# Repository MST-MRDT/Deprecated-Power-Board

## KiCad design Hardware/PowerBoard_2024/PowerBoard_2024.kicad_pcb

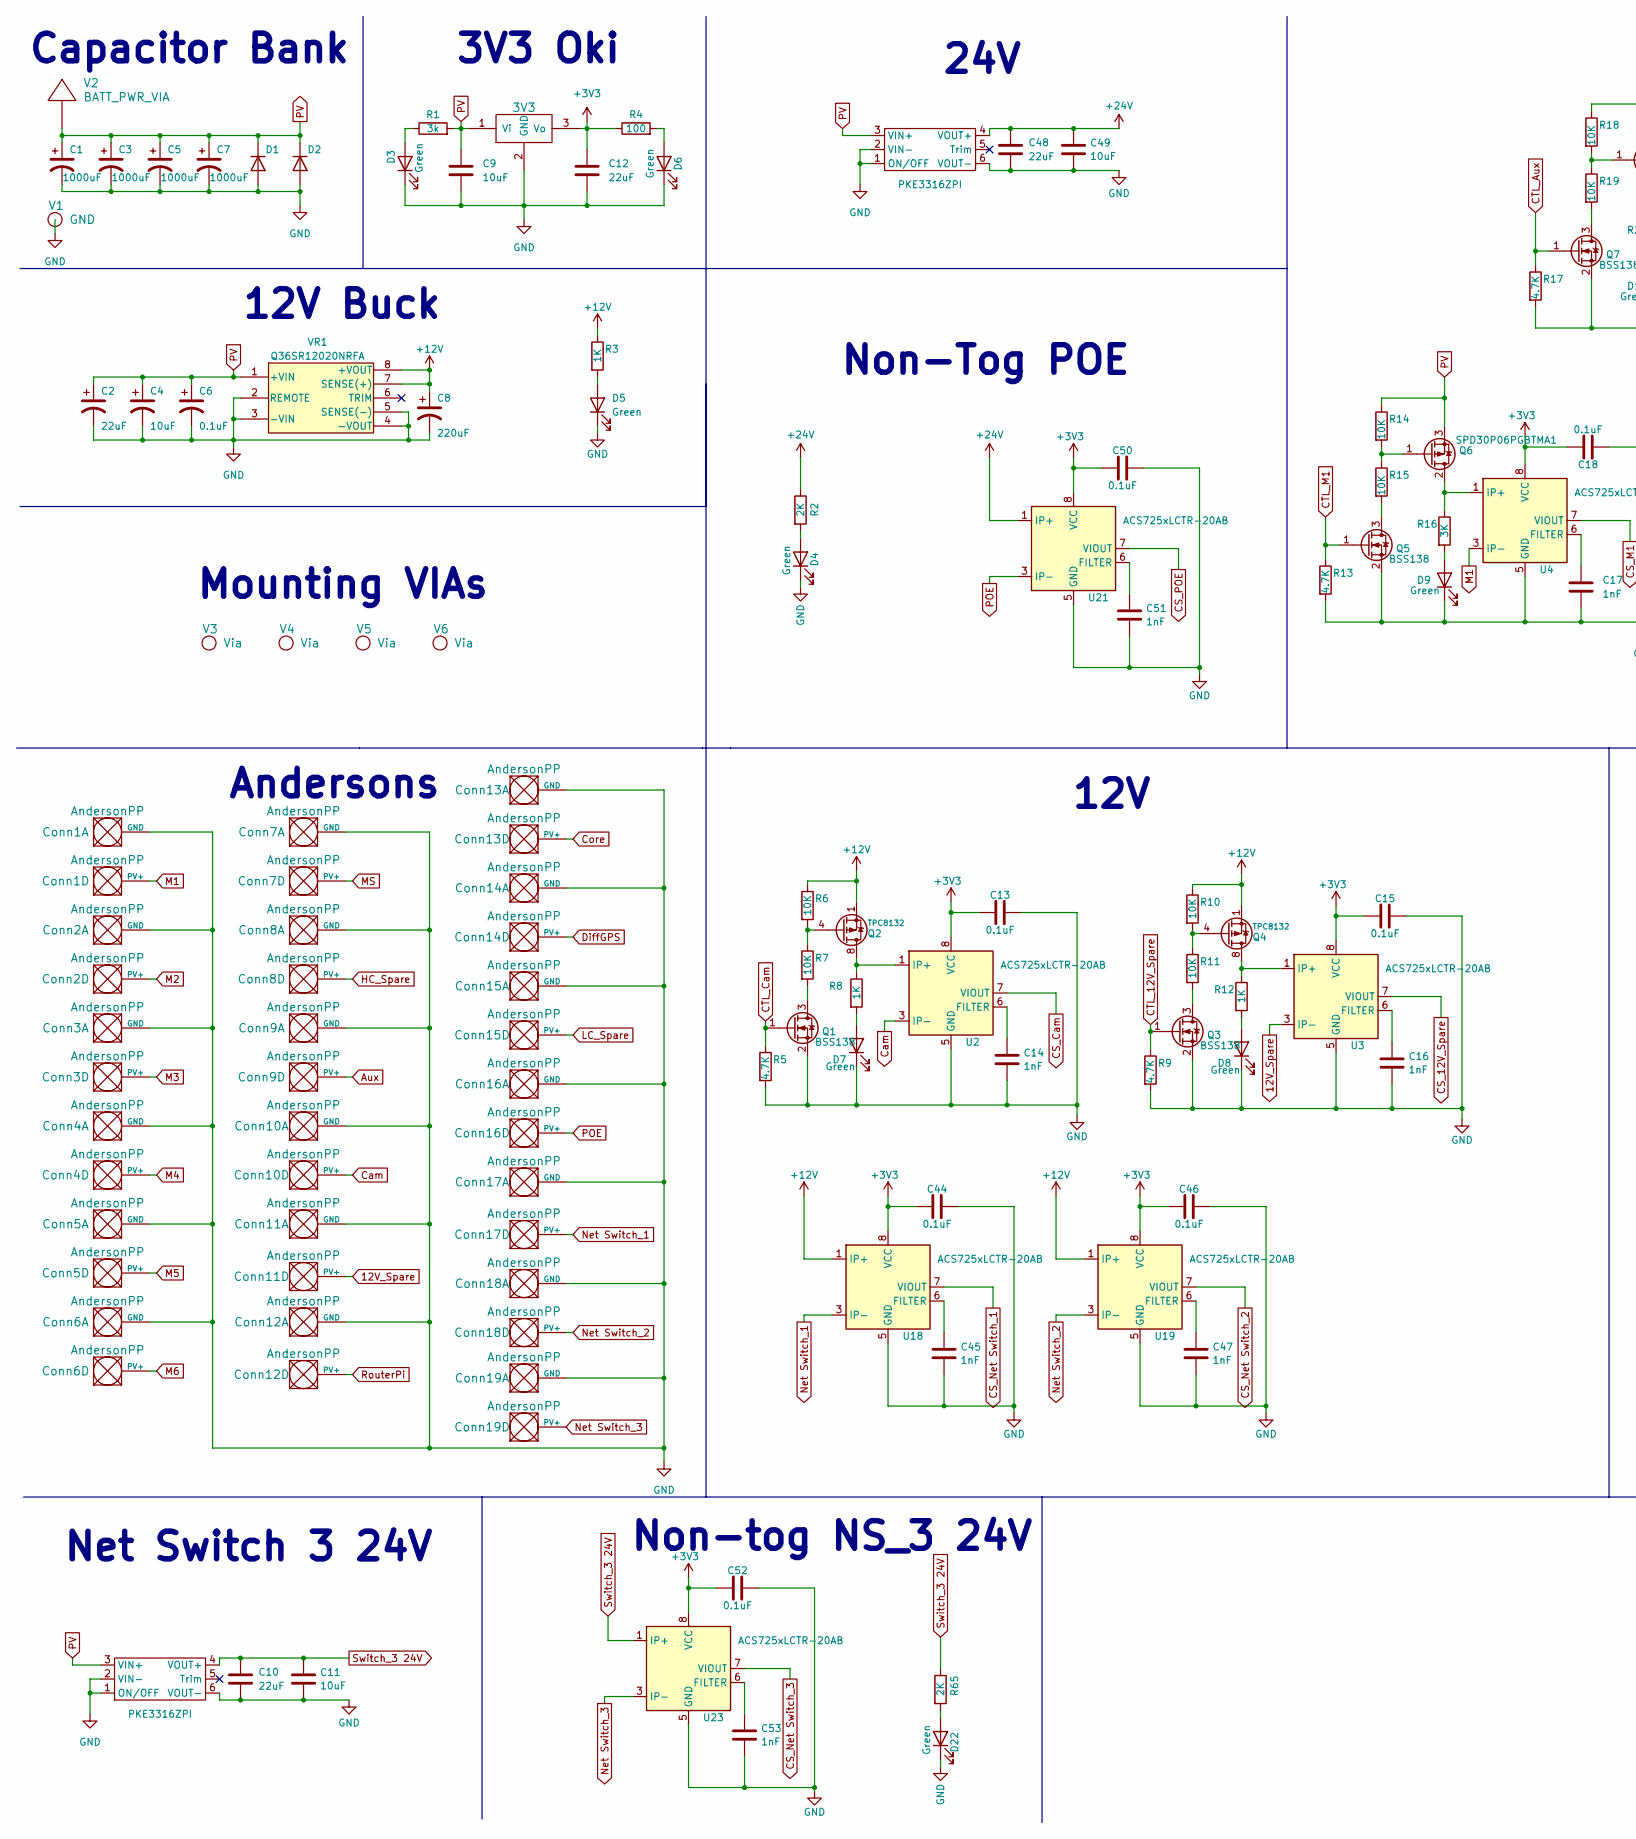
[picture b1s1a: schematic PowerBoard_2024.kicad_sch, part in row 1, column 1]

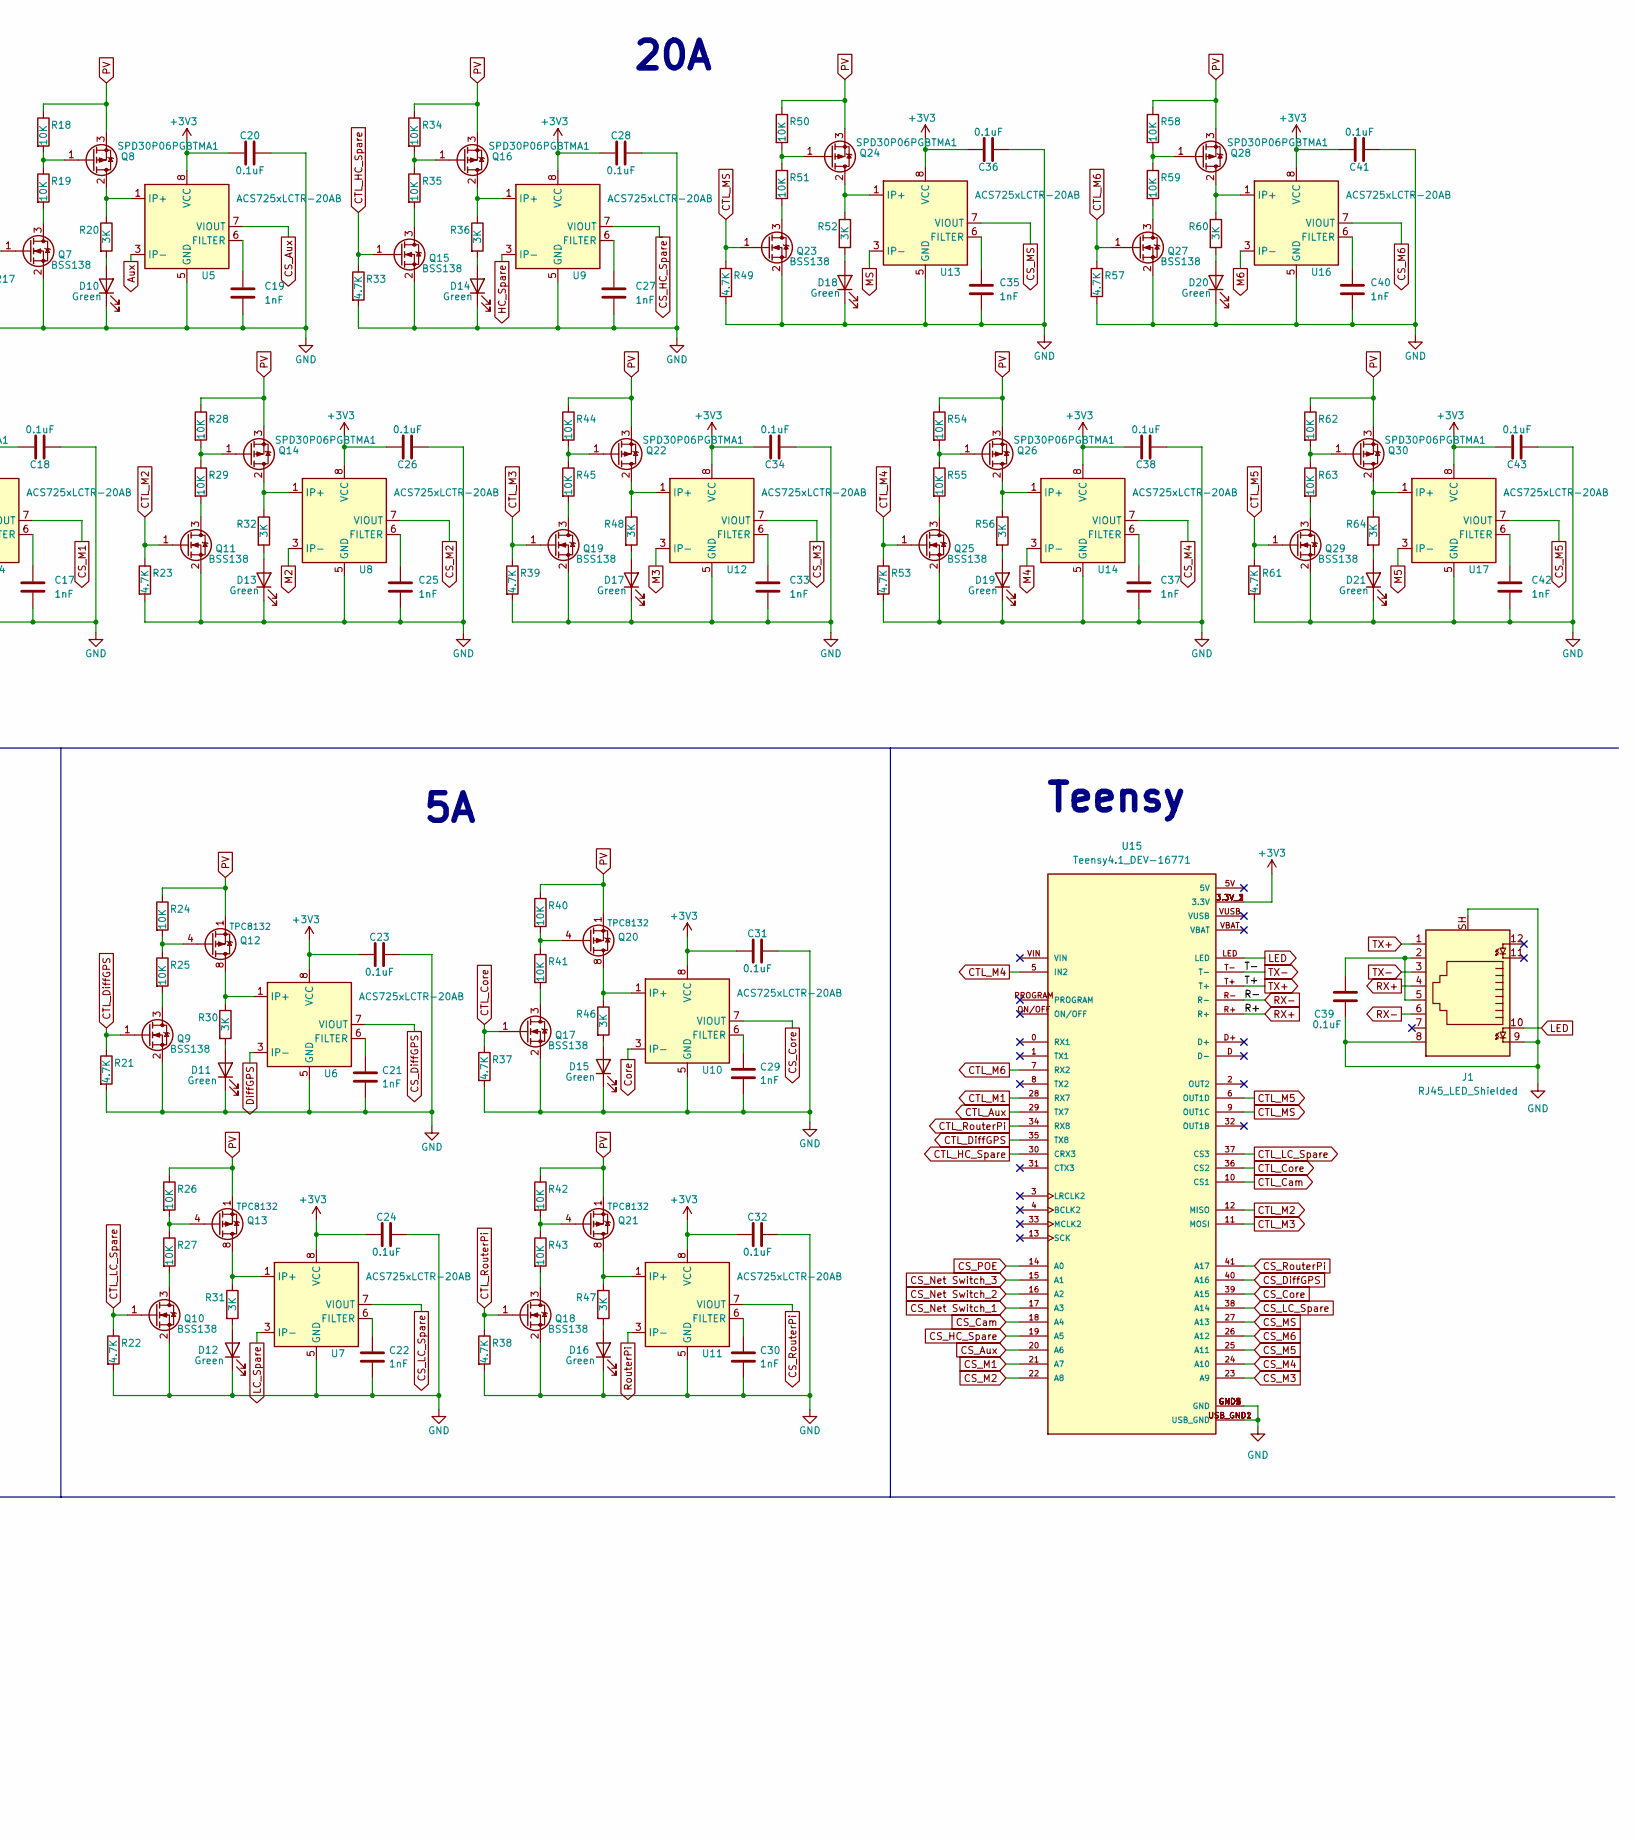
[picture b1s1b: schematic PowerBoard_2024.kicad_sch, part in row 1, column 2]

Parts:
C1, C3, C5, C7: 1000uF; CP_Radial_D16.0mm_P7.50mm
C2, C10, C48: 22uF; CP_Radial_D5.0mm_P2.00mm
C4, C9, C11, C49: 10uF; C_1206_3216Metric_Pad1.33x1.80mm_HandSolder
C6: 0.1uF; C_1206_3216Metric_Pad1.33x1.80mm_HandSolder
C8: 220uF; CP_Radial_D6.3mm_P2.50mm
C12: 22uF; C_0603_1608Metric_Pad1.08x0.95mm_HandSolder
C13, C15, C18, C20, C23, C24, C26, C28, C31, C32, C34, C36, C38, C39, C41, C43, C44, C46, C50, C52: 0.1uF; C_0603_1608Metric_Pad1.08x0.95mm_HandSolder
C14, C16, C17, C19, C21, C22, C25, C27, C29, C30, C33, C35, C37, C40, C42, C45, C47, C51, C53: 1nF; C_0603_1608Metric_Pad1.08x0.95mm_HandSolder
Conn1, Conn2, Conn3, Conn4, Conn5, Conn6, Conn7, Conn8, Conn9, Conn10, Conn11, Conn12, Conn13, Conn14, Conn15, Conn16, Conn17, Conn18, Conn19: AndersonPP; Square_Anderson_2_H_Stacked
D1, D2: 1.5KE36A+; D_DO-201_P5.08mm_Vertical_KathodeUp
D3, D4, D5, D6, D7, D8, D9, D10, D11, D12, D13, D14, D15, D16, D17, D18, D19, D20, D21, D22: Green; LED_0603_1608Metric_Pad1.05x0.95mm_HandSolder
J1: RJ45_LED_Shielded; RJ45_Teensy
Q1, Q3, Q5, Q7, Q9, Q10, Q11, Q15, Q17, Q18, Q19, Q23, Q25, Q27, Q29: BSS138; SOT-23
Q2, Q4, Q12, Q13, Q20, Q21: TPC8132; SOIC-8_3.9x4.9mm_P1.27mm
Q6, Q8, Q14, Q16, Q22, Q24, Q26, Q28, Q30: SPD30P06PGBTMA1; TO-252-2
R1: 3k; R_0603_1608Metric_Pad0.98x0.95mm_HandSolder
R2, R65: 2K; R_0603_1608Metric_Pad0.98x0.95mm_HandSolder
R3, R8, R12: 1K; R_0603_1608Metric_Pad0.98x0.95mm_HandSolder
R4: 100; R_0603_1608Metric_Pad0.98x0.95mm_HandSolder
R5, R9, R13, R17, R21, R22, R23, R33, R37, R38, R39, R49, R53, R57, R61: 4.7K; R_0603_1608Metric_Pad0.98x0.95mm_HandSolder
R6, R7, R10, R11, R14, R15, R18, R19, R24, R25, R26, R27, R28, R29, R34, R35, R40, R41, R42, R43, R44, R45, R50, R51, R54, R55, R58, R59, R62, R63: 10K; R_0603_1608Metric_Pad0.98x0.95mm_HandSolder
R16, R20, R30, R31, R32, R36, R46, R47, R48, R52, R56, R60, R64: 3K; R_0603_1608Metric_Pad0.98x0.95mm_HandSolder
U1: 3V3; OKI_Horizontal
U2, U3, U6, U7, U10, U11, U18, U19: ACS725xLCTR-20AB; SOP-8_3.9x4.9mm_P1.27mm
U4, U5, U8, U9, U12, U13, U14, U16, U17, U21, U23: ACS725xLCTR-20AB; SOIC-8_3.9x4.9mm_P1.27mm
U15: Teensy4.1_DEV-16771; Teensy_4_1_Ethernet; PARTREV 4.1
U20, U22: PKE3316ZPI
V1: GND; BATT_PWR_VIA
V2: BATT_PWR_VIA
V3, V4, V5, V6: Via; 4_40_Hole_Corner
VR1: Q36SR12020NRFA

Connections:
12V_Spare: Conn11.4 (PV+), U3.3 (IP-), U3.4 (IP-)
+3V3: C12.1, C13.1, C15.1, C18.2, C20.1, C23.1, C24.1, C26.2, C28.1, C31.1, C32.1, C34.2, C36.2, C38.2, C41.2, C43.2, C44.1, C46.1, C50.1, C52.1, R4.1, U1.3 (Vo), U2.8 (VCC), U3.8 (VCC), U4.8 (VCC), U5.8 (VCC), U6.8 (VCC), U7.8 (VCC), U8.8 (VCC), U9.8 (VCC), U10.8 (VCC), U11.8 (VCC), U12.8 (VCC), U13.8 (VCC), U14.8 (VCC), U15.3.3V_1 (3.3V), U15.3.3V_2 (3.3V), U15.3.3V_3 (3.3V), U16.8 (VCC), U17.8 (VCC), U18.8 (VCC), U19.8 (VCC), U21.8 (VCC), U23.8 (VCC)
+12V: C8.1, Q2.1 (S), Q2.2 (S), Q2.3 (S), Q4.1 (S), Q4.2 (S), Q4.3 (S), R3.1, R6.1, R10.1, U18.1 (IP+), U18.2 (IP+), U19.1 (IP+), U19.2 (IP+), VR1.7 (SENSE(+)), VR1.8 (+VOUT)
+24V: C48.1, C49.1, R2.1, U20.4 (VOUT+), U21.1 (IP+), U21.2 (IP+)
Aux: Conn9.4 (PV+), U5.3 (IP-), U5.4 (IP-)
CS_12V_Spare: U3.7 (VIOUT)
CS_Aux: U5.7 (VIOUT), U15.20 (A6)
CS_Cam: U2.7 (VIOUT), U15.18 (A4)
CS_Core: U10.7 (VIOUT), U15.39 (A15)
CS_DiffGPS: U6.7 (VIOUT), U15.40 (A16)
CS_HC_Spare: U9.7 (VIOUT), U15.19 (A5)
CS_LC_Spare: U7.7 (VIOUT), U15.38 (A14)
CS_M1: U4.7 (VIOUT), U15.21 (A7)
CS_M2: U8.7 (VIOUT), U15.22 (A8)
CS_M3: U12.7 (VIOUT), U15.23 (A9)
CS_M4: U14.7 (VIOUT), U15.24 (A10)
CS_M5: U15.25 (A11), U17.7 (VIOUT)
CS_M6: U15.26 (A12), U16.7 (VIOUT)
CS_MS: U13.7 (VIOUT), U15.27 (A13)
CS_Net Switch_1: U15.17 (A3), U18.7 (VIOUT)
CS_Net Switch_2: U15.16 (A2), U19.7 (VIOUT)
CS_Net Switch_3: U15.15 (A1), U23.7 (VIOUT)
CS_POE: U15.14 (A0), U21.7 (VIOUT)
CS_RouterPi: U11.7 (VIOUT), U15.41 (A17)
CTL_12V_Spare: Q3.1 (G), R9.1
CTL_Aux: Q7.1 (G), R17.1, U15.29 (TX7)
CTL_Cam: Q1.1 (G), R5.1, U15.10 (CS1)
CTL_Core: Q17.1 (G), R37.1, U15.36 (CS2)
CTL_DiffGPS: Q9.1 (G), R21.1, U15.35 (TX8)
CTL_HC_Spare: Q15.1 (G), R33.1, U15.30 (CRX3)
CTL_LC_Spare: Q10.1 (G), R22.1, U15.37 (CS3)
CTL_M1: Q5.1 (G), R13.1, U15.28 (RX7)
CTL_M2: Q11.1 (G), R23.1, U15.12 (MISO)
CTL_M3: Q19.1 (G), R39.1, U15.11 (MOSI)
CTL_M4: Q25.1 (G), R53.1, U15.5 (IN2)
CTL_M5: Q29.1 (G), R61.1, U15.6 (OUT1D)
CTL_M6: Q27.1 (G), R57.1, U15.7 (RX2)
CTL_MS: Q23.1 (G), R49.1, U15.9 (OUT1C)
CTL_RouterPi: Q18.1 (G), R38.1, U15.34 (RX8)
Cam: Conn10.4 (PV+), U2.3 (IP-), U2.4 (IP-)
Core: Conn13.4 (PV+), U10.3 (IP-), U10.4 (IP-)
DiffGPS: Conn14.4 (PV+), U6.3 (IP-), U6.4 (IP-)
GND: C1.2, C2.2, C3.2, C4.2, C5.2, C6.2, C7.2, C8.2, C9.2, C10.2, C11.2, C12.2, C13.2, C14.1, C15.2, C16.1, C17.2, C18.1, C19.1, C20.2, C21.1, C22.1, C23.2, C24.2, C25.2, C26.1, C27.1, C28.2, C29.1, C30.1, C31.2, C32.2, C33.2, C34.1, C35.2, C36.1, C37.2, C38.1, C39.1, C40.2, C41.1, C42.2, C43.1, C44.2, C45.1, C46.2, C47.1, C48.2, C49.2, C50.2, C51.1, C52.2, C53.1, Conn1.1 (GND), Conn2.1 (GND), Conn3.1 (GND), Conn4.1 (GND), Conn5.1 (GND), Conn6.1 (GND), Conn7.1 (GND), Conn8.1 (GND), Conn9.1 (GND), Conn10.1 (GND), Conn11.1 (GND), Conn12.1 (GND), Conn13.1 (GND), Conn14.1 (GND), Conn15.1 (GND), Conn16.1 (GND), Conn17.1 (GND), Conn18.1 (GND), Conn19.1 (GND), D1.2 (A), D2.2 (A), D3.1 (K), D4.1 (K), D5.1 (K), D6.1 (K), D7.1 (K), D8.1 (K), D9.1 (K), D10.1 (K), D11.1 (K), D12.1 (K), D13.1 (K), D14.1 (K), D15.1 (K), D16.1 (K), D17.1 (K), D18.1 (K), D19.1 (K), D20.1 (K), D21.1 (K), D22.1 (K), J1.8, J1.9, J1.SH, Q1.2 (S), Q3.2 (S), Q5.2 (S), Q7.2 (S), Q9.2 (S), Q10.2 (S), Q11.2 (S), Q15.2 (S), Q17.2 (S), Q18.2 (S), Q19.2 (S), Q23.2 (S), Q25.2 (S), Q27.2 (S), Q29.2 (S), R5.2, R9.2, R13.2, R17.2, R21.2, R22.2, R23.2, R33.2, R37.2, R38.2, R39.2, R49.2, R53.2, R57.2, R61.2, U1.2 (GND), U2.5 (GND), U3.5 (GND), U4.5 (GND), U5.5 (GND), U6.5 (GND), U7.5 (GND), U8.5 (GND), U9.5 (GND), U10.5 (GND), U11.5 (GND), U12.5 (GND), U13.5 (GND), U14.5 (GND), U15.GND1 (GND), U15.GND2 (GND), U15.GND3 (GND), U15.GND4 (GND), U15.GND5 (GND), U15.USB_GND1 (USB_GND), U15.USB_GND2 (USB_GND), U16.5 (GND), U17.5 (GND), U18.5 (GND), U19.5 (GND), U20.1 (ON/OFF), U20.2 (VIN-), U20.6 (VOUT-), U21.5 (GND), U22.1 (ON/OFF), U22.2 (VIN-), U22.6 (VOUT-), U23.5 (GND), V1.1, VR1.2 (REMOTE), VR1.3 (-VIN), VR1.4 (-VOUT), VR1.5 (SENSE(-))
HC_Spare: Conn8.4 (PV+), U9.3 (IP-), U9.4 (IP-)
LC_Spare: Conn15.4 (PV+), U7.3 (IP-), U7.4 (IP-)
LED: J1.10, U15.LED
M1: Conn1.4 (PV+), U4.3 (IP-), U4.4 (IP-)
M2: Conn2.4 (PV+), U8.3 (IP-), U8.4 (IP-)
M3: Conn3.4 (PV+), U12.3 (IP-), U12.4 (IP-)
M4: Conn4.4 (PV+), U14.3 (IP-), U14.4 (IP-)
M5: Conn5.4 (PV+), U17.3 (IP-), U17.4 (IP-)
M6: Conn6.4 (PV+), U16.3 (IP-), U16.4 (IP-)
MS: Conn7.4 (PV+), U13.3 (IP-), U13.4 (IP-)
Net Switch_1: Conn17.4 (PV+), U18.3 (IP-), U18.4 (IP-)
Net Switch_2: Conn18.4 (PV+), U19.3 (IP-), U19.4 (IP-)
Net Switch_3: Conn19.4 (PV+), U23.3 (IP-), U23.4 (IP-)
unnamed: C39.2, J1.2, J1.5
unnamed: D3.2 (A), R1.1
unnamed: D4.2 (A), R2.2
unnamed: D5.2 (A), R3.2
unnamed: D6.2 (A), R4.2
unnamed: D7.2 (A), R8.2
unnamed: D8.2 (A), R12.2
unnamed: D9.2 (A), R16.2
unnamed: D10.2 (A), R20.2
unnamed: D11.2 (A), R30.2
unnamed: D12.2 (A), R31.2
unnamed: D13.2 (A), R32.2
unnamed: D14.2 (A), R36.2
unnamed: D15.2 (A), R46.2
unnamed: D16.2 (A), R47.2
unnamed: D17.2 (A), R48.2
unnamed: D18.2 (A), R52.2
unnamed: D19.2 (A), R56.2
unnamed: D20.2 (A), R60.2
unnamed: D21.2 (A), R64.2
unnamed: D22.2 (A), R65.2
unnamed: Q1.3 (D), R7.2
unnamed: Q2.5 (D), Q2.6 (D), Q2.7 (D), Q2.8 (D), R8.1, U2.1 (IP+), U2.2 (IP+)
unnamed: Q2.4 (G), R6.2, R7.1
unnamed: Q3.3 (D), R11.2
unnamed: Q4.5 (D), Q4.6 (D), Q4.7 (D), Q4.8 (D), R12.1, U3.1 (IP+), U3.2 (IP+)
unnamed: Q4.4 (G), R10.2, R11.1
unnamed: Q5.3 (D), R15.2
unnamed: Q6.2 (D), R16.1, U4.1 (IP+), U4.2 (IP+)
unnamed: Q6.1 (G), R14.2, R15.1
unnamed: Q7.3 (D), R19.2
unnamed: Q8.2 (D), R20.1, U5.1 (IP+), U5.2 (IP+)
unnamed: Q8.1 (G), R18.2, R19.1
unnamed: Q9.3 (D), R25.2
unnamed: Q10.3 (D), R27.2
unnamed: Q11.3 (D), R29.2
unnamed: Q12.5 (D), Q12.6 (D), Q12.7 (D), Q12.8 (D), R30.1, U6.1 (IP+), U6.2 (IP+)
unnamed: Q12.4 (G), R24.2, R25.1
unnamed: Q13.5 (D), Q13.6 (D), Q13.7 (D), Q13.8 (D), R31.1, U7.1 (IP+), U7.2 (IP+)
unnamed: Q13.4 (G), R26.2, R27.1
unnamed: Q14.2 (D), R32.1, U8.1 (IP+), U8.2 (IP+)
unnamed: Q14.1 (G), R28.2, R29.1
unnamed: Q15.3 (D), R35.2
unnamed: Q16.2 (D), R36.1, U9.1 (IP+), U9.2 (IP+)
unnamed: Q16.1 (G), R34.2, R35.1
unnamed: Q17.3 (D), R41.2
unnamed: Q18.3 (D), R43.2
unnamed: Q19.3 (D), R45.2
unnamed: Q20.5 (D), Q20.6 (D), Q20.7 (D), Q20.8 (D), R46.1, U10.1 (IP+), U10.2 (IP+)
unnamed: Q20.4 (G), R40.2, R41.1
unnamed: Q21.5 (D), Q21.6 (D), Q21.7 (D), Q21.8 (D), R47.1, U11.1 (IP+), U11.2 (IP+)
unnamed: Q21.4 (G), R42.2, R43.1
unnamed: Q22.2 (D), R48.1, U12.1 (IP+), U12.2 (IP+)
unnamed: Q22.1 (G), R44.2, R45.1
unnamed: Q23.3 (D), R51.2
unnamed: Q24.2 (D), R52.1, U13.1 (IP+), U13.2 (IP+)
unnamed: Q24.1 (G), R50.2, R51.1
unnamed: Q25.3 (D), R55.2
unnamed: Q26.2 (D), R56.1, U14.1 (IP+), U14.2 (IP+)
unnamed: Q26.1 (G), R54.2, R55.1
unnamed: Q27.3 (D), R59.2
unnamed: Q28.2 (D), R60.1, U16.1 (IP+), U16.2 (IP+)
unnamed: Q28.1 (G), R58.2, R59.1
unnamed: Q29.3 (D), R63.2
unnamed: Q30.2 (D), R64.1, U17.1 (IP+), U17.2 (IP+)
unnamed: Q30.1 (G), R62.2, R63.1
unnamed: C14.2, U2.6 (FILTER)
unnamed: C16.2, U3.6 (FILTER)
unnamed: C17.1, U4.6 (FILTER)
unnamed: C19.2, U5.6 (FILTER)
unnamed: C21.2, U6.6 (FILTER)
unnamed: C22.2, U7.6 (FILTER)
unnamed: C25.1, U8.6 (FILTER)
unnamed: C27.2, U9.6 (FILTER)
unnamed: C29.2, U10.6 (FILTER)
unnamed: C30.2, U11.6 (FILTER)
unnamed: C33.1, U12.6 (FILTER)
unnamed: C35.1, U13.6 (FILTER)
unnamed: C37.1, U14.6 (FILTER)
unnamed: C40.1, U16.6 (FILTER)
unnamed: C42.1, U17.6 (FILTER)
unnamed: C45.2, U18.6 (FILTER)
unnamed: C47.2, U19.6 (FILTER)
unnamed: C51.2, U21.6 (FILTER)
unnamed: C53.2, U23.6 (FILTER)
POE: Conn16.4 (PV+), U21.3 (IP-), U21.4 (IP-)
PV: C1.1, C2.1, C3.1, C4.1, C5.1, C6.1, C7.1, C9.1, D1.1 (K), D2.1 (K), Q6.3 (S), Q8.3 (S), Q12.1 (S), Q12.2 (S), Q12.3 (S), Q13.1 (S), Q13.2 (S), Q13.3 (S), Q14.3 (S), Q16.3 (S), Q20.1 (S), Q20.2 (S), Q20.3 (S), Q21.1 (S), Q21.2 (S), Q21.3 (S), Q22.3 (S), Q24.3 (S), Q26.3 (S), Q28.3 (S), Q30.3 (S), R1.2, R14.1, R18.1, R24.1, R26.1, R28.1, R34.1, R40.1, R42.1, R44.1, R50.1, R54.1, R58.1, R62.1, U1.1 (Vi), U20.3 (VIN+), U22.3 (VIN+), V2.1, VR1.1 (+VIN)
RX+: J1.4, U15.R+
RX-: J1.6, U15.R-
RouterPi: Conn12.4 (PV+), U11.3 (IP-), U11.4 (IP-)
Switch_3 24V: C10.1, C11.1, R65.1, U22.4 (VOUT+), U23.1 (IP+), U23.2 (IP+)
TX+: J1.1, U15.T+
TX-: J1.3, U15.T-

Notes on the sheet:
24V
Teensy
12V Buck
Andersons
20A
Capacitor Bank
12V
Non-tog NS_3 24V
Mounting VIAs
Net Switch 3 24V
3V3 Oki
Non-Tog POE

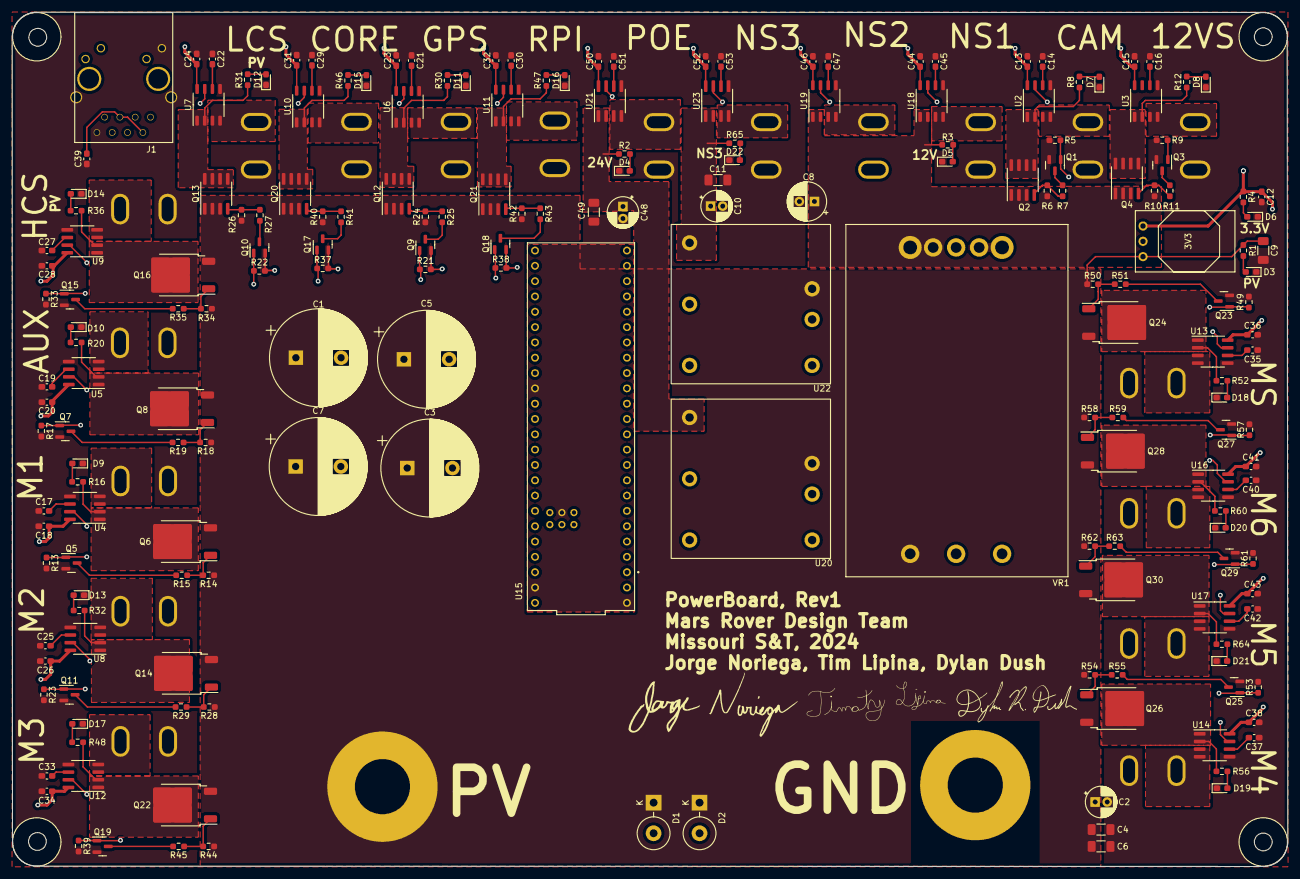
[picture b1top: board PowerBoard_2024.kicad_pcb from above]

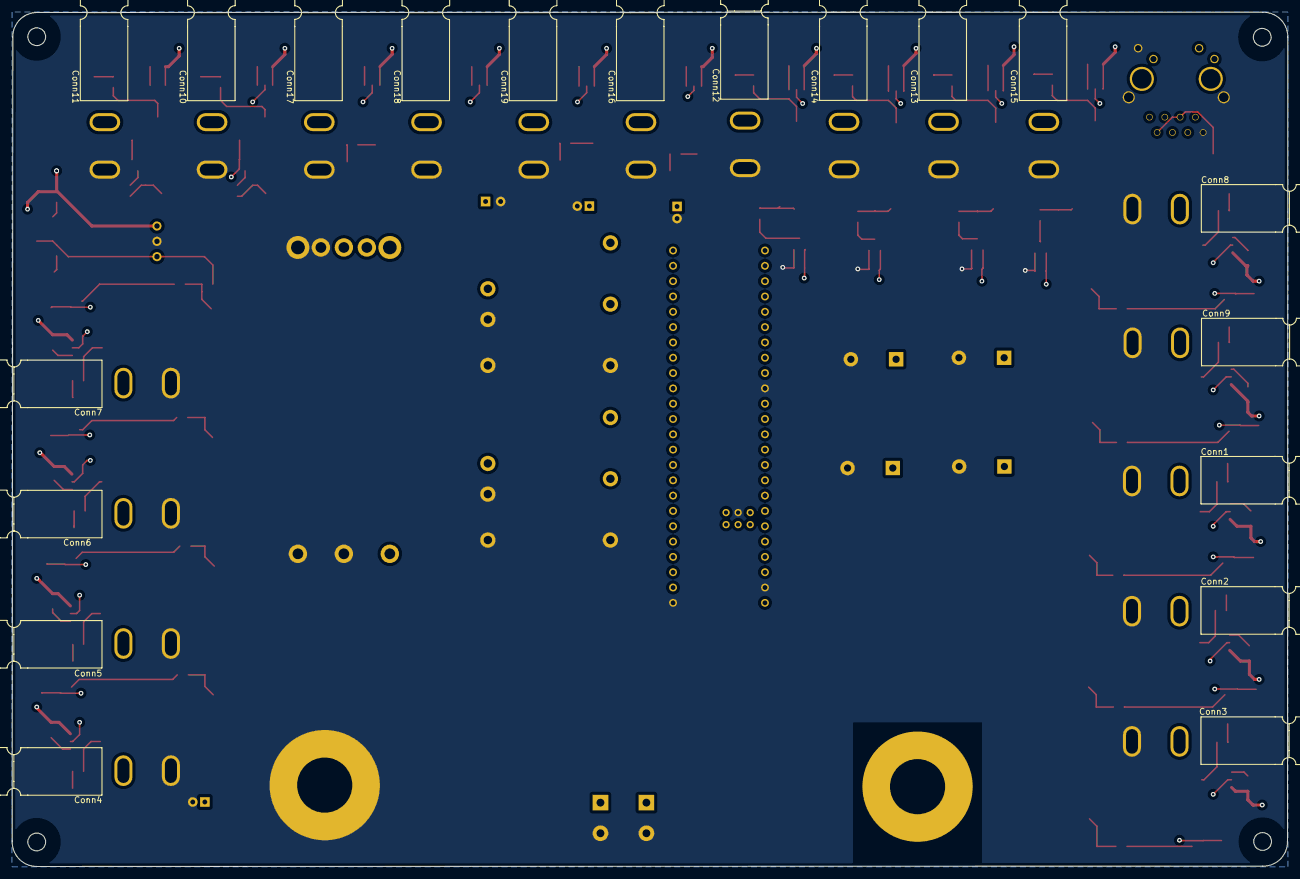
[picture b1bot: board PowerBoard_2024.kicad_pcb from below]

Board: 4 copper layers, 211.5 x 141.6 mm, 220 parts (19 on the bottom side), 148 nets.

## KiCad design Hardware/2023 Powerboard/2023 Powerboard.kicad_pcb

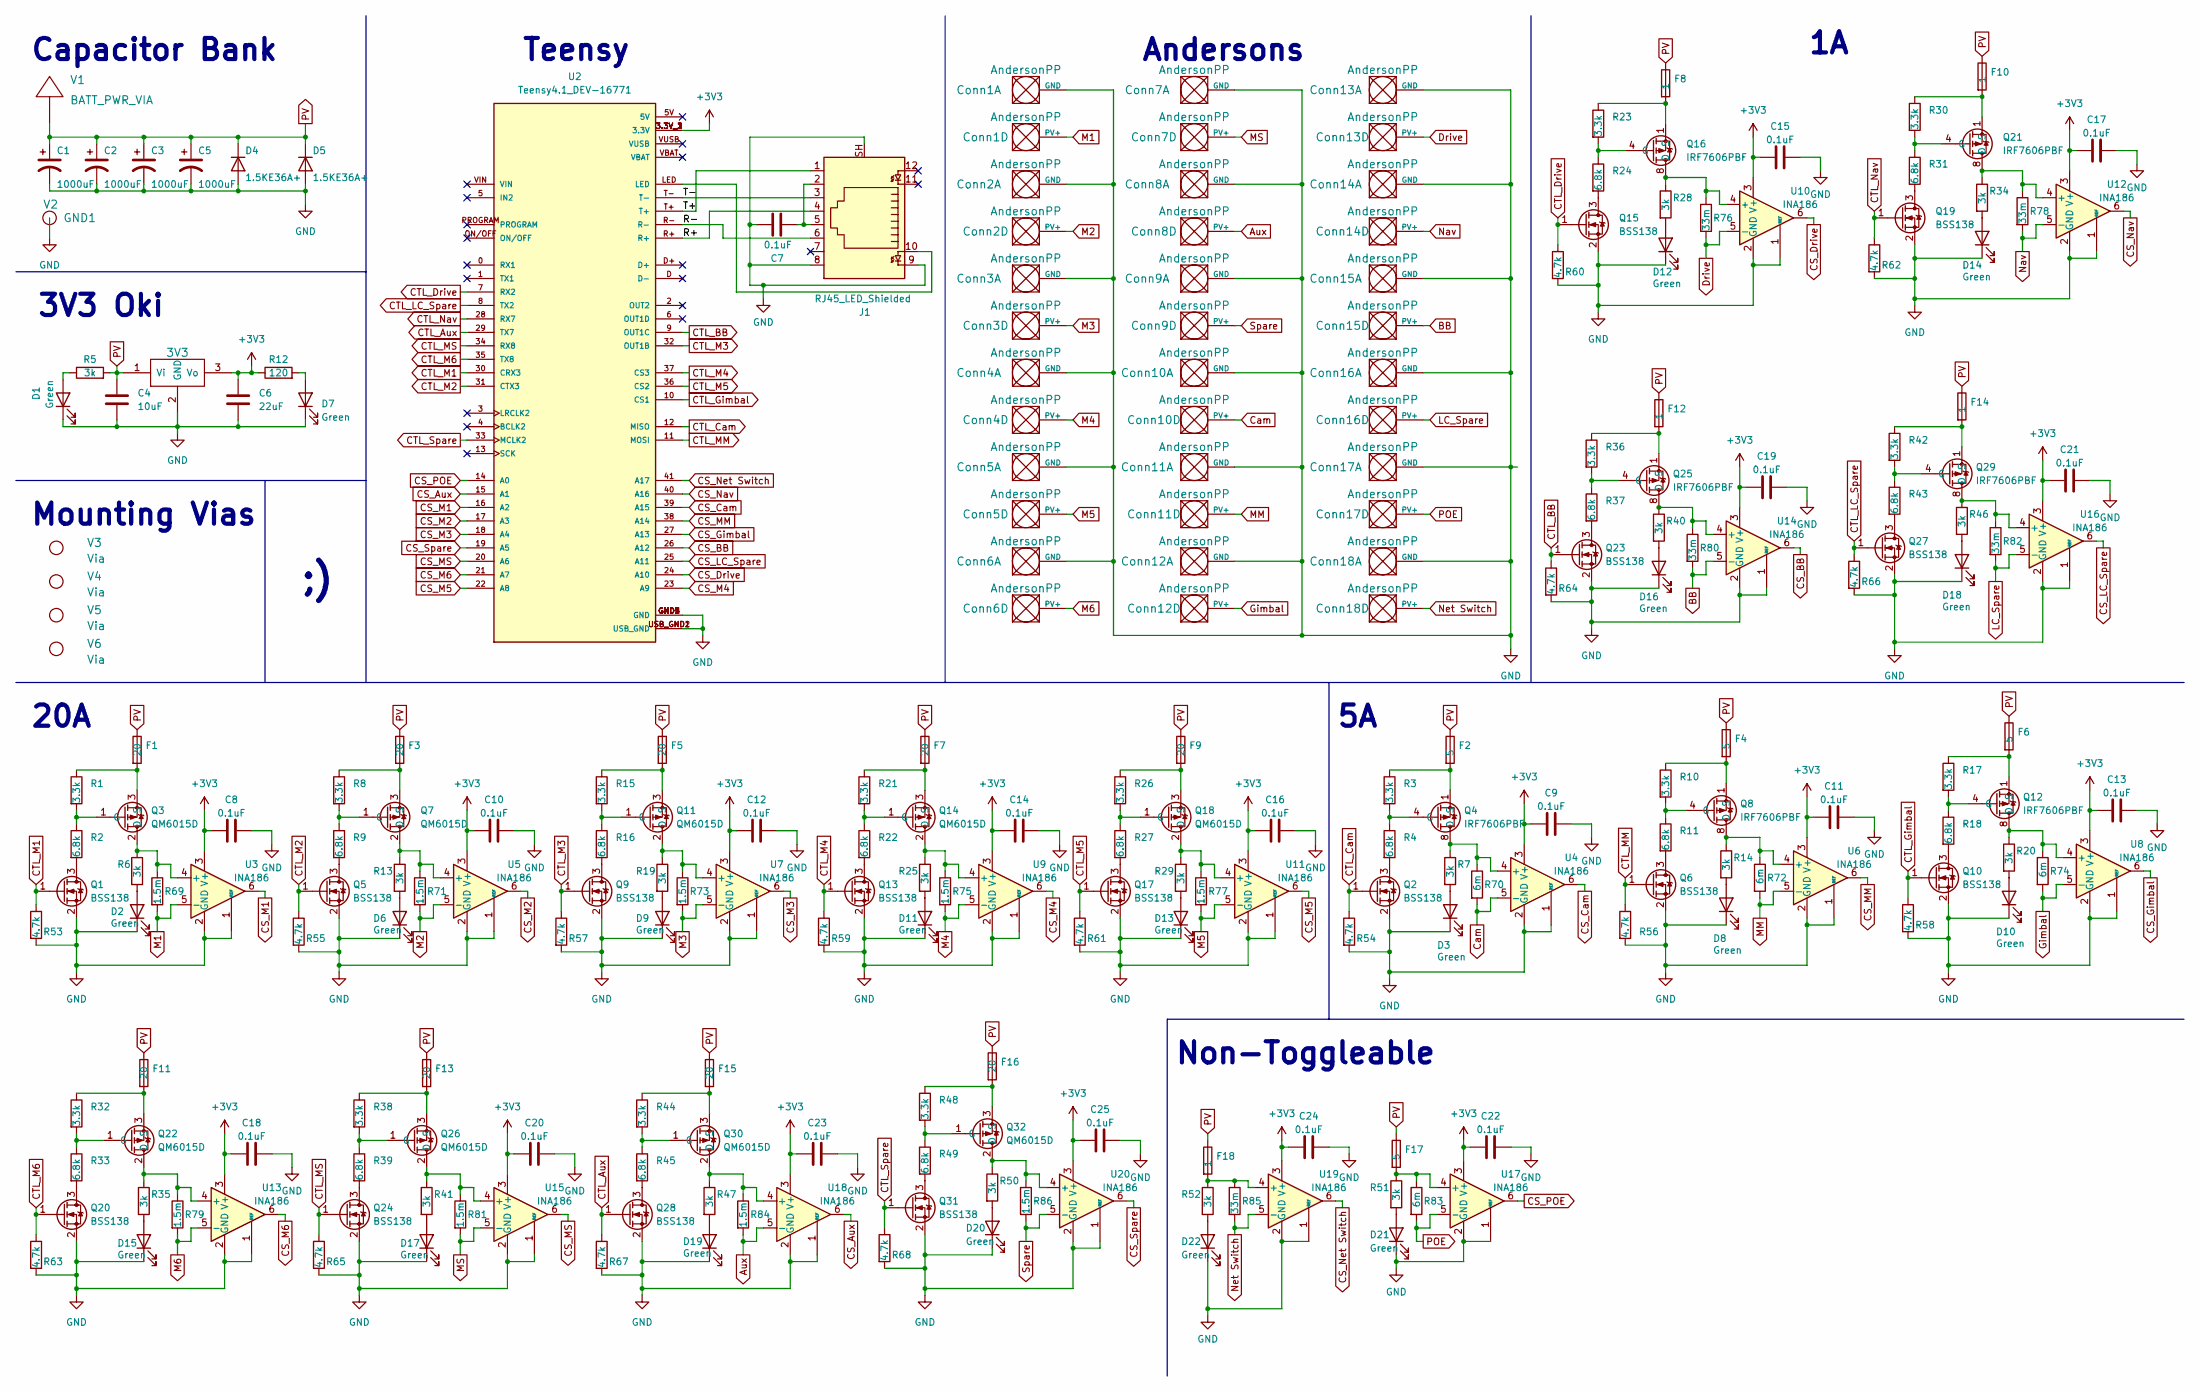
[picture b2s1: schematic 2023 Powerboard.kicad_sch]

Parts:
C1, C2, C3, C5: 1000uF; CP_Radial_D16.0mm_P7.50mm
C4: 10uF; C_0603_1608Metric_Pad1.08x0.95mm_HandSolder
C6: 22uF; C_0603_1608Metric_Pad1.08x0.95mm_HandSolder
C7, C8, C9, C10, C11, C12, C13, C14, C15, C16, C17, C18, C19, C20, C21, C22, C23, C24, C25: 0.1uF; C_0603_1608Metric_Pad1.08x0.95mm_HandSolder
Conn1, Conn2, Conn3, Conn4, Conn5, Conn6, Conn7, Conn8, Conn9, Conn10, Conn11, Conn12, Conn13, Conn14, Conn15, Conn16, Conn17, Conn18: AndersonPP; Square_Anderson_2_H_Stacked
D1, D2, D3, D6, D7, D8, D9, D10, D11, D12, D13, D14, D15, D16, D17, D18, D19, D20, D21, D22: Green; LED_0603_1608Metric_Pad1.05x0.95mm_HandSolder
D4, D5: 1.5KE36A+; D_DO-201_P5.08mm_Vertical_KathodeUp
F1, F3, F5, F7, F9, F11, F13, F15, F16: 20; ATC_Fuse_Block
F2, F4, F6, F17: 5; ATC_Fuse_Block
F8, F10, F12, F14, F18: 1; ATC_Fuse_Block
J1: RJ45_LED_Shielded; RJ45_Teensy
Q1, Q2, Q5, Q6, Q9, Q10, Q13, Q15, Q17, Q19, Q20, Q23, Q24, Q27, Q28, Q31: BSS138; SOT-23
Q3, Q7, Q11, Q14, Q18, Q22, Q26, Q30, Q32: QM6015D; TO-252-2
Q4, Q8, Q12, Q16, Q21, Q25, Q29: IRF7606PBF; SOP-8_3.9x4.9mm_P1.27mm
R1, R3, R8, R10, R15, R17, R21, R23, R26, R30, R32, R36, R38, R42, R44, R48: 3.3k; R_0603_1608Metric_Pad0.98x0.95mm_HandSolder
R2, R4, R9, R11, R16, R18, R22, R24, R27, R31, R33, R37, R39, R43, R45, R49: 6.8k; R_0603_1608Metric_Pad0.98x0.95mm_HandSolder
R5, R6, R7, R13, R14, R19, R20, R25, R28, R29, R34, R35, R40, R41, R46, R47, R50, R51, R52: 3k; R_0603_1608Metric_Pad0.98x0.95mm_HandSolder
R12: 120; R_0603_1608Metric_Pad0.98x0.95mm_HandSolder
R53, R54, R55, R56, R57, R58, R59, R60, R61, R62, R63, R64, R65, R66, R67, R68: 4.7k; R_0603_1608Metric_Pad0.98x0.95mm_HandSolder
R69, R71, R73, R75, R77, R79, R81, R84, R86: 1.5m; R_2512_6332Metric_Pad1.40x3.35mm_HandSolder
R70, R72, R74, R83: 6m; R_0603_1608Metric_Pad0.98x0.95mm_HandSolder
R76, R78, R80, R82, R85: 33m; R_0603_1608Metric_Pad0.98x0.95mm_HandSolder
U1: 3V3; OKI_Horizontal
U2: Teensy4.1_DEV-16771; Teensy_4_1_Ethernet; PARTREV 4.1
U3, U4, U5, U6, U7, U8, U9, U10, U11, U12, U13, U14, U15, U16, U17, U18, U19, U20: INA186; SOT-363_SC-70-6_Handsoldering
V1: BATT_PWR_VIA
V2: GND1; BATT_PWR_VIA
V3, V4, V5, V6: Via; 4_40_Hole_Corner

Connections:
+3V3: C6.1, C8.1, C9.1, C10.1, C11.1, C12.1, C13.1, C14.1, C15.1, C16.1, C17.1, C18.1, C19.1, C20.1, C21.1, C22.1, C23.1, C24.1, C25.1, R12.1, U1.3 (Vo), U2.3.3V_1 (3.3V), U2.3.3V_2 (3.3V), U2.3.3V_3 (3.3V), U3.3 (V+), U4.3 (V+), U5.3 (V+), U6.3 (V+), U7.3 (V+), U8.3 (V+), U9.3 (V+), U10.3 (V+), U11.3 (V+), U12.3 (V+), U13.3 (V+), U14.3 (V+), U15.3 (V+), U16.3 (V+), U17.3 (V+), U18.3 (V+), U19.3 (V+), U20.3 (V+)
/R+: J1.4, U2.R+
/R-: J1.6, U2.R-
/T+: J1.1, U2.T+
/T-: J1.3, U2.T-
Aux: Conn8.4 (PV+), R84.2, U18.5 (-)
BB: Conn15.4 (PV+), R80.2, U14.5 (-)
CS_Aux: U2.15 (A1), U18.6
CS_BB: U2.26 (A12), U14.6
CS_Cam: U2.39 (A15), U4.6
CS_Drive: U2.24 (A10), U10.6
CS_Gimbal: U2.27 (A13), U8.6
CS_LC_Spare: U2.25 (A11), U16.6
CS_M1: U2.16 (A2), U3.6
CS_M2: U2.17 (A3), U5.6
CS_M3: U2.18 (A4), U7.6
CS_M4: U2.23 (A9), U9.6
CS_M5: U2.22 (A8), U11.6
CS_M6: U2.21 (A7), U13.6
CS_MM: U2.38 (A14), U6.6
CS_MS: U2.20 (A6), U15.6
CS_Nav: U2.40 (A16), U12.6
CS_Net Switch: U2.41 (A17), U19.6
CS_POE: U2.14 (A0), U17.6
CS_Spare: U2.19 (A5), U20.6
CTL_Aux: Q28.1 (G), R67.1, U2.29 (TX7)
CTL_BB: Q23.1 (G), R64.1, U2.9 (OUT1C)
CTL_Cam: Q2.1 (G), R54.1, U2.12 (MISO)
CTL_Drive: Q15.1 (G), R60.1, U2.7 (RX2)
CTL_Gimbal: Q10.1 (G), R58.1, U2.10 (CS1)
CTL_LC_Spare: Q27.1 (G), R66.1, U2.8 (TX2)
CTL_M1: Q1.1 (G), R53.1, U2.30 (CRX3)
CTL_M2: Q5.1 (G), R55.1, U2.31 (CTX3)
CTL_M3: Q9.1 (G), R57.1, U2.32 (OUT1B)
CTL_M4: Q13.1 (G), R59.1, U2.37 (CS3)
CTL_M5: Q17.1 (G), R61.1, U2.36 (CS2)
CTL_M6: Q20.1 (G), R63.1, U2.35 (TX8)
CTL_MM: Q6.1 (G), R56.1, U2.11 (MOSI)
CTL_MS: Q24.1 (G), R65.1, U2.34 (RX8)
CTL_Nav: Q19.1 (G), R62.1, U2.28 (RX7)
CTL_Spare: Q31.1 (G), R68.1, U2.33 (MCLK2)
Cam: Conn10.4 (PV+), R70.2, U4.5 (-)
Drive: Conn13.4 (PV+), R76.2, U10.5 (-)
GND: C1.2, C2.2, C3.2, C4.2, C5.2, C6.2, C7.2, C8.2, C9.2, C10.2, C11.2, C12.2, C13.2, C14.2, C15.2, C16.2, C17.2, C18.2, C19.2, C20.2, C21.2, C22.2, C23.2, C24.2, C25.2, Conn1.1 (GND), Conn2.1 (GND), Conn3.1 (GND), Conn4.1 (GND), Conn5.1 (GND), Conn6.1 (GND), Conn7.1 (GND), Conn8.1 (GND), Conn9.1 (GND), Conn10.1 (GND), Conn11.1 (GND), Conn12.1 (GND), Conn13.1 (GND), Conn14.1 (GND), Conn15.1 (GND), Conn16.1 (GND), Conn17.1 (GND), Conn18.1 (GND), D1.1 (K), D2.1 (K), D3.1 (K), D4.1 (A), D5.1 (A), D6.1 (K), D7.1 (K), D8.1 (K), D9.1 (K), D10.1 (K), D11.1 (K), D12.1 (K), D13.1 (K), D14.1 (K), D15.1 (K), D16.1 (K), D17.1 (K), D18.1 (K), D19.1 (K), D20.1 (K), D21.1 (K), D22.1 (K), J1.8, J1.9, J1.SH, Q1.2 (S), Q2.2 (S), Q5.2 (S), Q6.2 (S), Q9.2 (S), Q10.2 (S), Q13.2 (S), Q15.2 (S), Q17.2 (S), Q19.2 (S), Q20.2 (S), Q23.2 (S), Q24.2 (S), Q27.2 (S), Q28.2 (S), Q31.2 (S), R53.2, R54.2, R55.2, R56.2, R57.2, R58.2, R59.2, R60.2, R61.2, R62.2, R63.2, R64.2, R65.2, R66.2, R67.2, R68.2, U1.2 (GND), U2.GND1 (GND), U2.GND2 (GND), U2.GND3 (GND), U2.GND4 (GND), U2.GND5 (GND), U2.USB_GND1 (USB_GND), U2.USB_GND2 (USB_GND), U3.1 (REF), U3.2 (GND), U4.1 (REF), U4.2 (GND), U5.1 (REF), U5.2 (GND), U6.1 (REF), U6.2 (GND), U7.1 (REF), U7.2 (GND), U8.1 (REF), U8.2 (GND), U9.1 (REF), U9.2 (GND), U10.1 (REF), U10.2 (GND), U11.1 (REF), U11.2 (GND), U12.1 (REF), U12.2 (GND), U13.1 (REF), U13.2 (GND), U14.1 (REF), U14.2 (GND), U15.1 (REF), U15.2 (GND), U16.1 (REF), U16.2 (GND), U17.1 (REF), U17.2 (GND), U18.1 (REF), U18.2 (GND), U19.1 (REF), U19.2 (GND), U20.1 (REF), U20.2 (GND), V2.1
Gimbal: Conn12.4 (PV+), R74.2, U8.5 (-)
LC_Spare: Conn16.4 (PV+), R82.2, U16.5 (-)
M1: Conn1.4 (PV+), R69.2, U3.5 (-)
M2: Conn2.4 (PV+), R71.2, U5.5 (-)
M3: Conn3.4 (PV+), R73.2, U7.5 (-)
M4: Conn4.4 (PV+), R75.2, U9.5 (-)
M5: Conn5.4 (PV+), R77.2, U11.5 (-)
M6: Conn6.4 (PV+), R79.2, U13.5 (-)
MM: Conn11.4 (PV+), R72.2, U6.5 (-)
MS: Conn7.4 (PV+), R81.2, U15.5 (-)
Nav: Conn14.4 (PV+), R78.2, U12.5 (-)
Net Switch: Conn18.4 (PV+), R85.2, U19.5 (-)
unnamed: C7.1, J1.2, J1.5
unnamed: D1.2 (A), R5.1
unnamed: D2.2 (A), R6.2
unnamed: D3.2 (A), R7.2
unnamed: D6.2 (A), R13.2
unnamed: D7.2 (A), R12.2
unnamed: D8.2 (A), R14.2
unnamed: D9.2 (A), R19.2
unnamed: D10.2 (A), R20.2
unnamed: D11.2 (A), R25.2
unnamed: D12.2 (A), R28.2
unnamed: D13.2 (A), R29.2
unnamed: D14.2 (A), R34.2
unnamed: D15.2 (A), R35.2
unnamed: D16.2 (A), R40.2
unnamed: D17.2 (A), R41.2
unnamed: D18.2 (A), R46.2
unnamed: D19.2 (A), R47.2
unnamed: D20.2 (A), R50.2
unnamed: D21.2 (A), R51.2
unnamed: D22.2 (A), R52.2
unnamed: F1.2, Q3.3 (S), R1.1
unnamed: F2.2, Q4.1 (S), Q4.2 (S), Q4.3 (S), R3.1
unnamed: F3.2, Q7.3 (S), R8.1
unnamed: F4.2, Q8.1 (S), Q8.2 (S), Q8.3 (S), R10.1
unnamed: F5.2, Q11.3 (S), R15.1
unnamed: F6.2, Q12.1 (S), Q12.2 (S), Q12.3 (S), R17.1
unnamed: F7.2, Q14.3 (S), R21.1
unnamed: F8.2, Q16.1 (S), Q16.2 (S), Q16.3 (S), R23.1
unnamed: F9.2, Q18.3 (S), R26.1
unnamed: F10.2, Q21.1 (S), Q21.2 (S), Q21.3 (S), R30.1
unnamed: F11.2, Q22.3 (S), R32.1
unnamed: F12.2, Q25.1 (S), Q25.2 (S), Q25.3 (S), R36.1
unnamed: F13.2, Q26.3 (S), R38.1
unnamed: F14.2, Q29.1 (S), Q29.2 (S), Q29.3 (S), R42.1
unnamed: F15.2, Q30.3 (S), R44.1
unnamed: F16.2, Q32.3 (S), R48.1
unnamed: F17.2, R51.1, R83.1, U17.4 (+)
unnamed: F18.2, R52.1, R85.1, U19.4 (+)
unnamed: J1.10, U2.LED
unnamed: Q1.3 (D), R2.2
unnamed: Q2.3 (D), R4.2
unnamed: Q3.1 (G), R1.2, R2.1
unnamed: Q3.2 (D), R6.1, R69.1, U3.4 (+)
unnamed: Q4.4 (G), R3.2, R4.1
unnamed: Q4.5 (D), Q4.6 (D), Q4.7 (D), Q4.8 (D), R7.1, R70.1, U4.4 (+)
unnamed: Q5.3 (D), R9.2
unnamed: Q6.3 (D), R11.2
unnamed: Q7.1 (G), R8.2, R9.1
unnamed: Q7.2 (D), R13.1, R71.1, U5.4 (+)
unnamed: Q8.4 (G), R10.2, R11.1
unnamed: Q8.5 (D), Q8.6 (D), Q8.7 (D), Q8.8 (D), R14.1, R72.1, U6.4 (+)
unnamed: Q9.3 (D), R16.2
unnamed: Q10.3 (D), R18.2
unnamed: Q11.1 (G), R15.2, R16.1
unnamed: Q11.2 (D), R19.1, R73.1, U7.4 (+)
unnamed: Q12.4 (G), R17.2, R18.1
unnamed: Q12.5 (D), Q12.6 (D), Q12.7 (D), Q12.8 (D), R20.1, R74.1, U8.4 (+)
unnamed: Q13.3 (D), R22.2
unnamed: Q14.1 (G), R21.2, R22.1
unnamed: Q14.2 (D), R25.1, R75.1, U9.4 (+)
unnamed: Q15.3 (D), R24.2
unnamed: Q16.4 (G), R23.2, R24.1
unnamed: Q16.5 (D), Q16.6 (D), Q16.7 (D), Q16.8 (D), R28.1, R76.1, U10.4 (+)
unnamed: Q17.3 (D), R27.2
unnamed: Q18.1 (G), R26.2, R27.1
unnamed: Q18.2 (D), R29.1, R77.1, U11.4 (+)
unnamed: Q19.3 (D), R31.2
unnamed: Q20.3 (D), R33.2
unnamed: Q21.4 (G), R30.2, R31.1
unnamed: Q21.5 (D), Q21.6 (D), Q21.7 (D), Q21.8 (D), R34.1, R78.1, U12.4 (+)
unnamed: Q22.1 (G), R32.2, R33.1
unnamed: Q22.2 (D), R35.1, R79.1, U13.4 (+)
unnamed: Q23.3 (D), R37.2
unnamed: Q24.3 (D), R39.2
unnamed: Q25.4 (G), R36.2, R37.1
unnamed: Q25.5 (D), Q25.6 (D), Q25.7 (D), Q25.8 (D), R40.1, R80.1, U14.4 (+)
unnamed: Q26.1 (G), R38.2, R39.1
unnamed: Q26.2 (D), R41.1, R81.1, U15.4 (+)
unnamed: Q27.3 (D), R43.2
unnamed: Q28.3 (D), R45.2
unnamed: Q29.4 (G), R42.2, R43.1
unnamed: Q29.5 (D), Q29.6 (D), Q29.7 (D), Q29.8 (D), R46.1, R82.1, U16.4 (+)
unnamed: Q30.1 (G), R44.2, R45.1
unnamed: Q30.2 (D), R47.1, R84.1, U18.4 (+)
unnamed: Q31.3 (D), R49.2
unnamed: Q32.1 (G), R48.2, R49.1
unnamed: Q32.2 (D), R50.1, R86.1, U20.4 (+)
POE: Conn17.4 (PV+), R83.2, U17.5 (-)
PV: C1.1, C2.1, C3.1, C4.1, C5.1, D4.2 (K), D5.2 (K), F1.1, F2.1, F3.1, F4.1, F5.1, F6.1, F7.1, F8.1, F9.1, F10.1, F11.1, F12.1, F13.1, F14.1, F15.1, F16.1, F17.1, F18.1, R5.2, U1.1 (Vi), V1.1
Spare: Conn9.4 (PV+), R86.2, U20.5 (-)

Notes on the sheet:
Mounting Vias
Teensy
3V3 Oki
20A
Non-Toggleable
Andersons
Capacitor Bank
